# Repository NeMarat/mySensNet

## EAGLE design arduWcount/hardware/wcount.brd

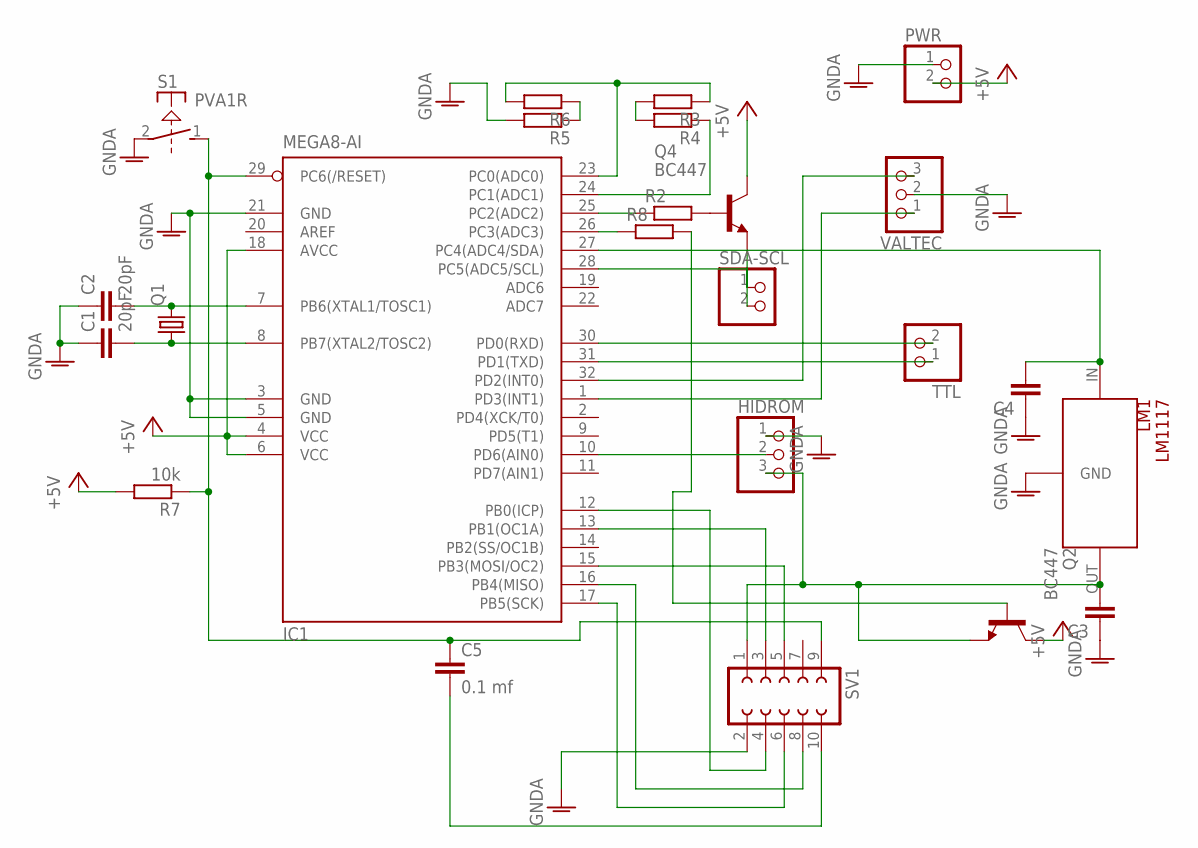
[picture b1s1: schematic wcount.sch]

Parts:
C1, C2: 20pF; C0805
C3, C4: C; C0805
C5: 0.1 mf; C0805
HIDROM: PINHD-1X3; 1X03
IC1: MEGA8-AI; TQFP32-08
LM1: LM1117; SOT223
PWR: PINHD-1X2; 1X02
Q1: CRYSTALHC49S; HC49/S
Q2, Q4: BC447; TO92-EBC
R2, R3, R4, R5, R6, R8: R-EU_R0805; R0805
R7: 10k; R0805
S1: PVA1R
SDA-SCL: PINHD-1X2; 1X02
SV1: FE05-2
TTL: PINHD-1X2; 1X02
VALTEC: PINHD-1X3; 1X03

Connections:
+5V: IC1.4 (VCC), IC1.6 (VCC), IC1.18 (AVCC), PWR.2, Q2.C, Q4.C, R7.2
GNDA: C1.1, C2.1, C3.1, C4.1, HIDROM.1, IC1.3 (GND), IC1.5 (GND), IC1.21 (GND), LM1.GND/ADJ (GND), PWR.1, R5.2, S1.2, SV1.2, VALTEC.2
unnamed: IC1.12 (PB0(ICP)), SV1.4
unnamed: C2.2, IC1.7 (PB6(XTAL1/TOSC1)), Q1.2
unnamed: IC1.30 (PD0(RXD)), TTL.2
unnamed: IC1.32 (PD2(INT0)), VALTEC.3
unnamed: IC1.31 (PD1(TXD)), TTL.1
unnamed: C4.2, LM1.IN, Q4.E
unnamed: IC1.24 (PC1(ADC1)), R4.1
unnamed: IC1.1 (PD3(INT1)), VALTEC.1
unnamed: IC1.25 (PC2(ADC2)), R2.1
unnamed: Q4.B, R2.2
unnamed: C3.2, HIDROM.3, LM1.OUT, Q2.E, SV1.1
unnamed: IC1.17 (PB5(SCK)), SV1.6
unnamed: R3.2, R4.2
unnamed: IC1.16 (PB4(MISO)), SV1.8
unnamed: IC1.13 (PB1(OC1A)), SV1.3
unnamed: IC1.15 (PB3(MOSI/OC2)), SV1.5
unnamed: C5.1, IC1.29 (PC6(/RESET)), R7.1, S1.1 (S), SV1.9
unnamed: IC1.23 (PC0(ADC0)), R3.1, R6.2
unnamed: IC1.27 (PC4(ADC4/SDA)), SDA-SCL.1
unnamed: IC1.28 (PC5(ADC5/SCL)), SDA-SCL.2
unnamed: R5.1, R6.1
unnamed: HIDROM.2, IC1.10 (PD6(AIN0))
unnamed: C1.2, IC1.8 (PB7(XTAL2/TOSC2)), Q1.1
unnamed: IC1.26 (PC3(ADC3)), R8.1
unnamed: Q2.B, R8.2
unnamed: C5.2, SV1.10

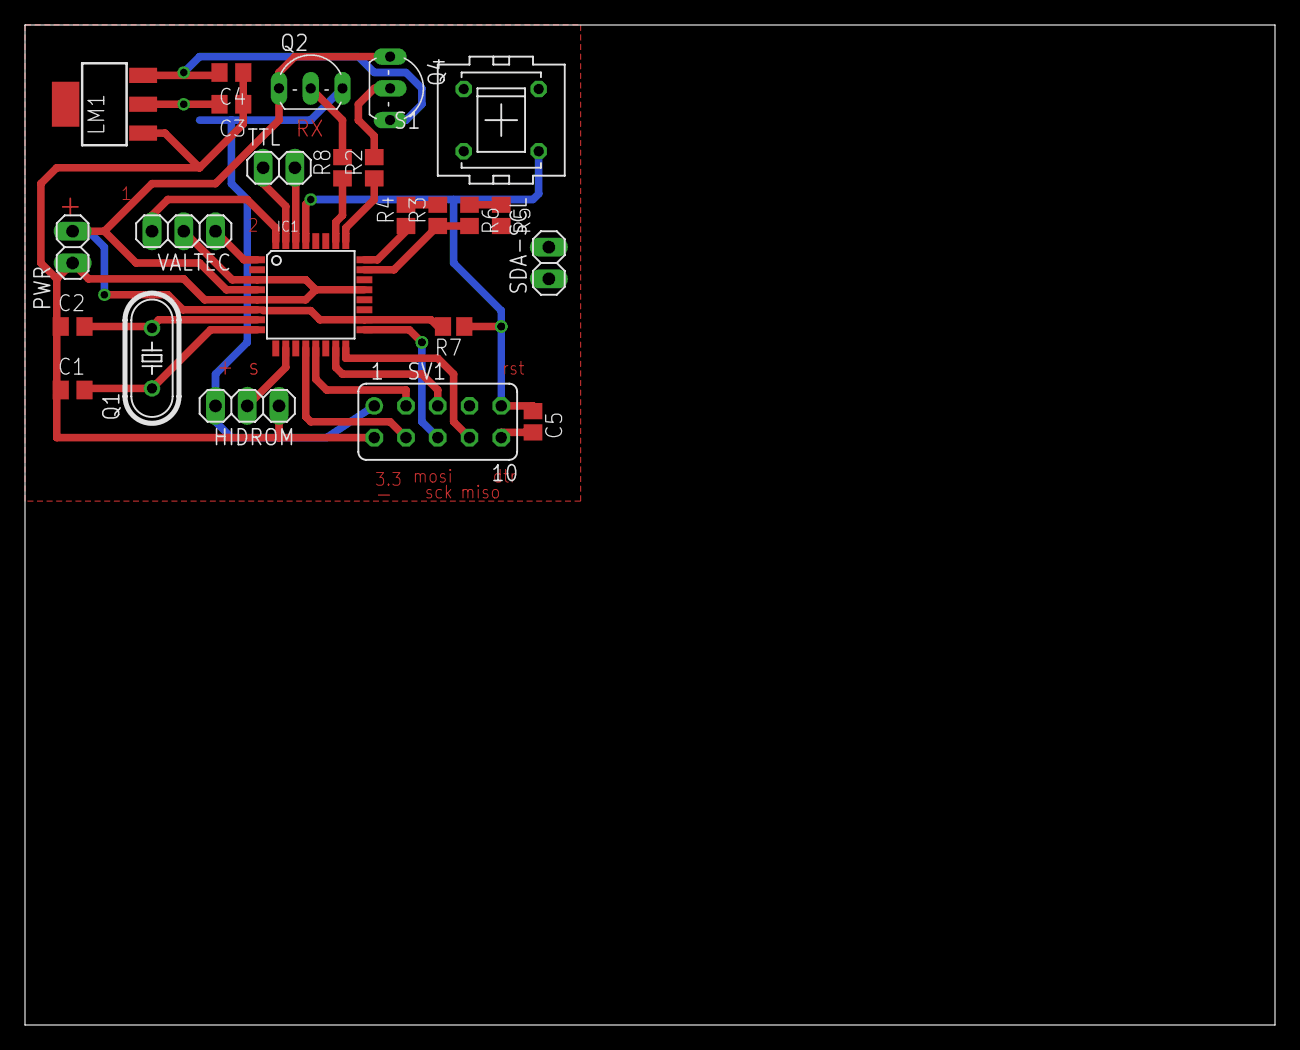
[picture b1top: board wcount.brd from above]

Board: 2 copper layers, 100.0 x 80.0 mm, 24 parts (0 on the bottom side), 28 nets.

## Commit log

2015-10-17 initial commmit
2015-10-17 New battarey test method. Also removed possible mistake: in test pins function situation on one could change state of other.
2015-10-19 EEPROM rotating added
2015-11-28 new sensor added
2015-11-30 watchdog added
2015-12-02 fine
2015-12-23 Led driver added
2016-01-10 villa defined for other house channel
2016-01-17 rf433 moved from hall sensor to leDriver
2016-02-07 ethernet gateway add
2016-03-12 Added Oregon weather sensor protocol. Not complete.
2016-03-19 oregon sensor reciever added to ledriver
2016-05-21 CO2 sensor based on MH-Z19 added
2016-05-21 removed crc control
2016-06-04 co2 sensor needs not more than 30 sec. interval between measurements. And not less 10 sec.
2016-07-17 Oregon now works
2016-11-19 Relay could be used as slow PWM: in type 1 you can send seconds in minute to be turned on. For use with heaters and PID controller
2016-11-22 flashind add to ledriver for using with doorbell
2016-11-22 experiment with ,ysensors strings
2017-04-09 energocount NG :)
2017-12-17 energo count new generation 3
2017-12-17 softserial configured 8 ardu pin - to tx pin, 7 ardu pin to rx
2017-12-25 it works well
